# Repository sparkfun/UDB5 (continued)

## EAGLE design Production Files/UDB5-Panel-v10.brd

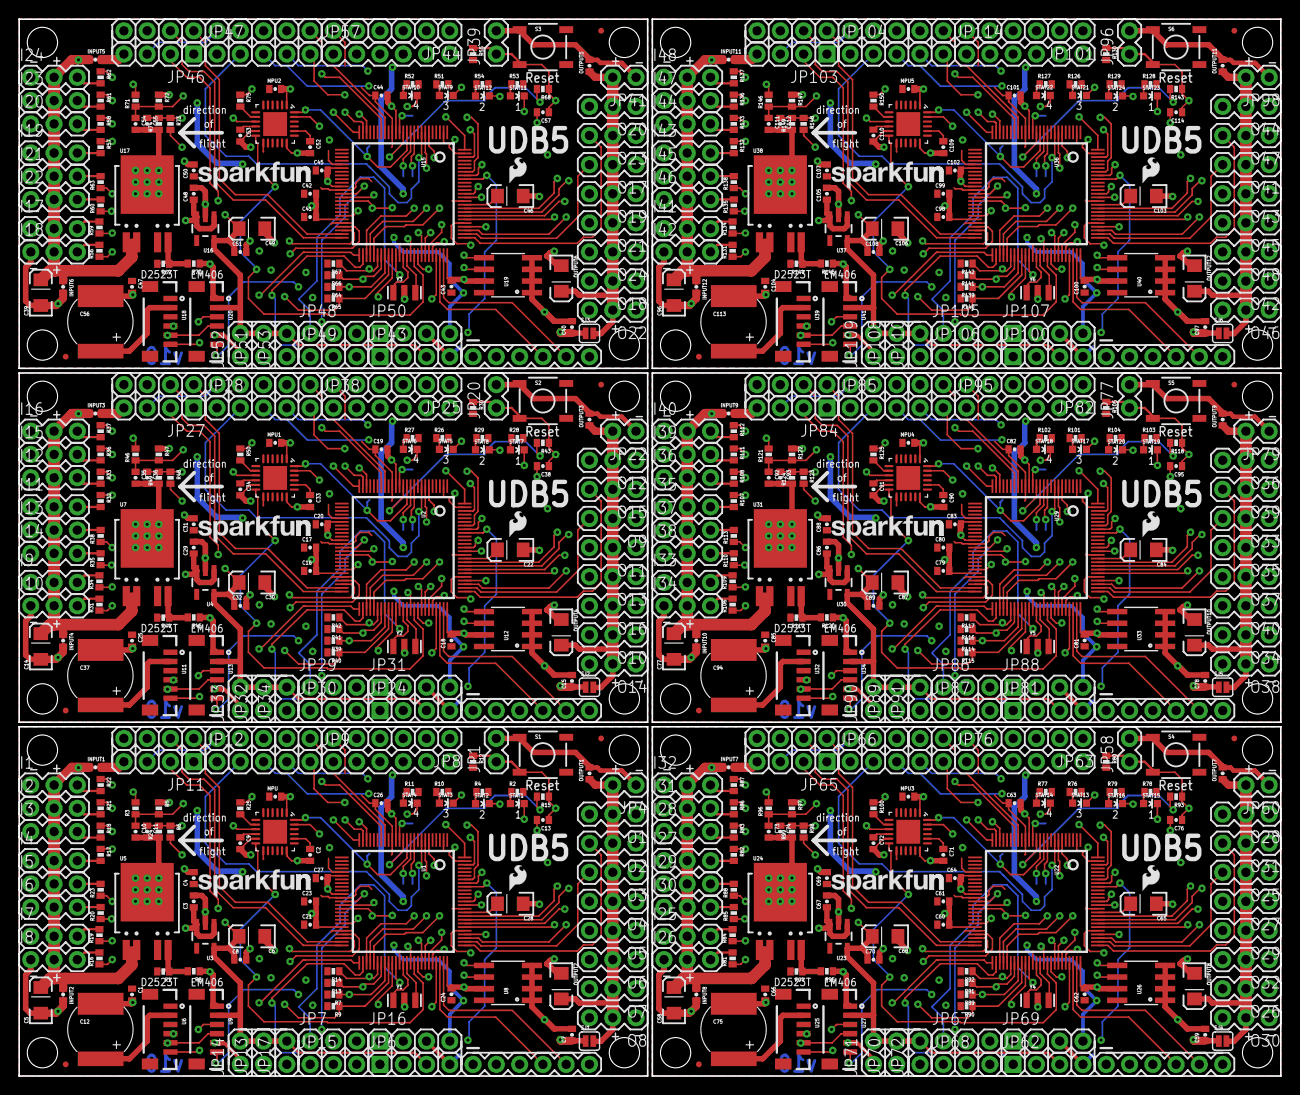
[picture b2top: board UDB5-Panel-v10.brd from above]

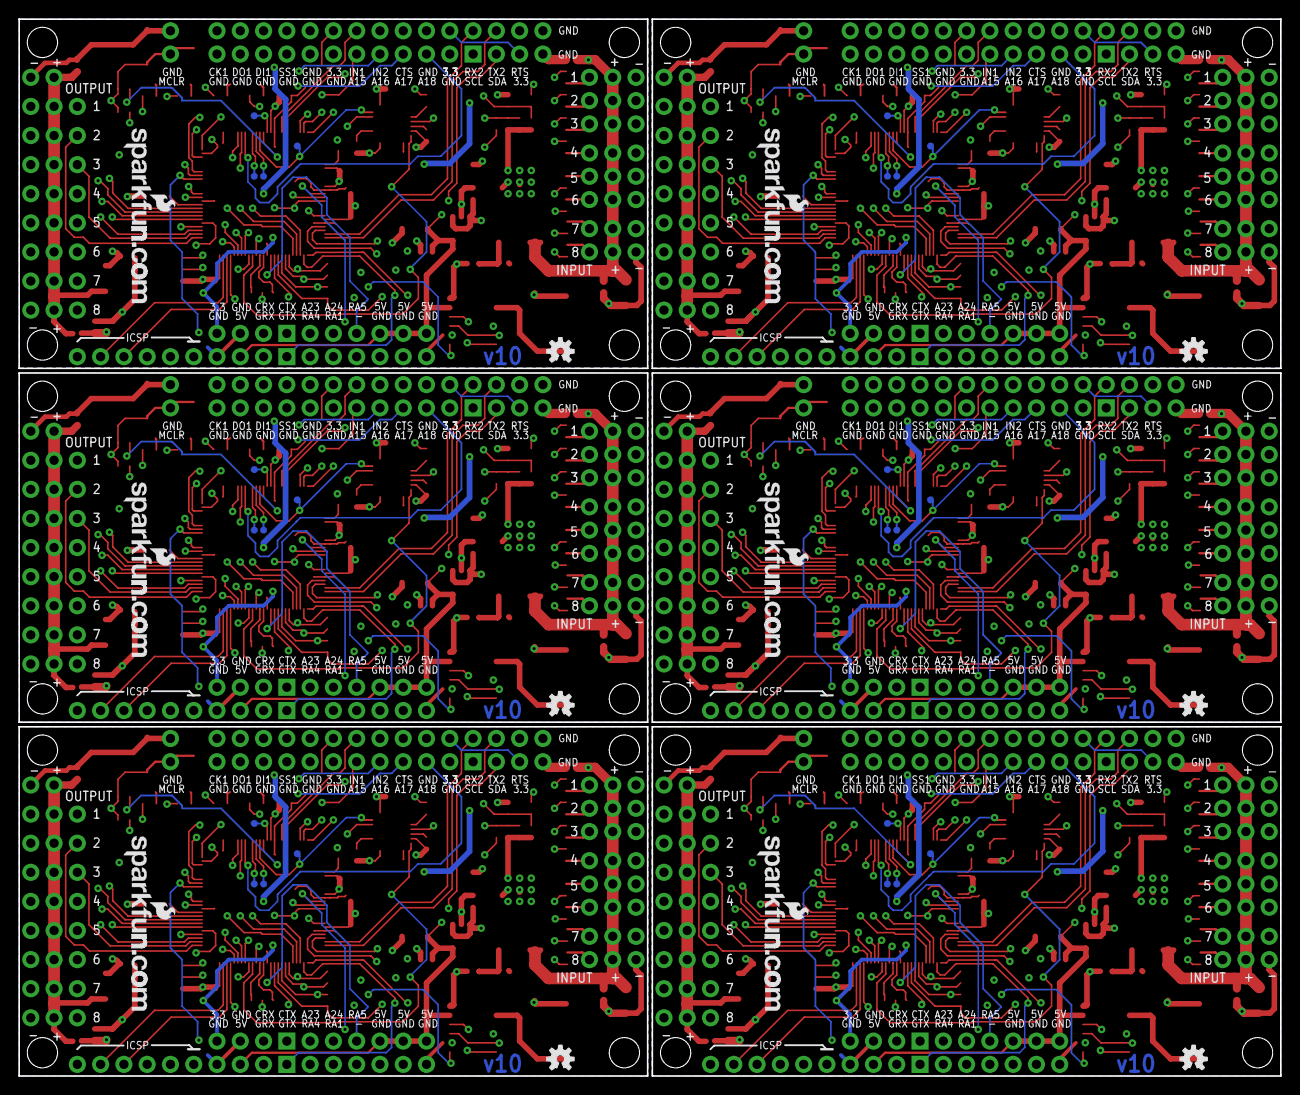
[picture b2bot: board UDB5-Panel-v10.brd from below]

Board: 4 copper layers, 137.7 x 115.3 mm, 654 parts (36 on the bottom side), 504 nets.

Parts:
C1, C3, C25, C29, C47, C48, C66, C67, C85, C86, C104, C105: 1uF; 0402-CAP
C2, C33, C52, C71, C90, C109: 2.2nF; 0402-CAP
C4, C7, C8, C9, C13, C15, C16, C17, C18, C19, C20, C21, C23, C24, C26, C27, C31, C32, C34, C38, C40, C41, C42, C43, C44, C45, C50, C51, C53, C57, C59, C60, C61, C62, C63, C64, C69, C70, C72, C76, C78, C79, C80, C81, C82, C83, C88, C89, C91, C95, C97, C98, C99, C100, C101, C102, C107, C108, C110, C114: 0.1uF; 0402-CAP
C5, C6, C14, C22, C28, C30, C39, C46, C49, C58, C65, C68, C77, C84, C87, C96, C103, C106: 10uF; EIA3216
C10, C11, C35, C36, C54, C55, C73, C74, C92, C93, C111, C112: 22nF; 0402-CAP
C12, C37, C56, C75, C94, C113: 0.2F/3.3V; EN_J2
I1, I2, I3, I4, I5, I6, I7, I8, I9, I10, I11, I12, I13, I14, I15, I16, I17, I18, I19, I20, I21, I22, I23, I24, I25, I26, I27, I28, I29, I30, I31, I32, I33, I34, I35, I36, I37, I38, I39, I40, I41, I42, I43, I44, I45, I46, I47, I48: S; 1X03
INPUT1, INPUT2, INPUT3, INPUT4, INPUT5, INPUT6, INPUT7, INPUT8, INPUT9, INPUT10, INPUT11, INPUT12: 0.1uF; 0402-CAP
JP1, JP20, JP39, JP58, JP77, JP96: EXT_Reset; 1X02
JP2, JP21, JP40, JP59, JP78, JP97: prog; 1X06
JP3, JP35, JP54, JP73, JP92, JP111: LOGO-SFENEW; SFE-NEW-WEBLOGO
JP4, JP22, JP41, JP60, JP79, JP98: SVCC; 1X02
JP5, JP23, JP42, JP61, JP80, JP99: ST; 1X07
JP6, JP24, JP43, JP62, JP81, JP100: SG; 1X04
JP7, JP15, JP29, JP30, JP48, JP49, JP67, JP68, JP86, JP87, JP105, JP106: extra; 1X03
JP8, JP25, JP44, JP63, JP82, JP101: SPI1; 1X06
JP9, JP38, JP57, JP76, JP95, JP114: GND; 1X06
JP10, JP26, JP45, JP64, JP83, JP102: INT; 1X02
JP11, JP27, JP46, JP65, JP84, JP103: I2C; 1X04
JP12, JP28, JP47, JP66, JP85, JP104: ACOM1; 1X05
JP13, JP14, JP17, JP32, JP33, JP34, JP51, JP52, JP53, JP70, JP71, JP72, JP89, JP90, JP91, JP108, JP109, JP110: power; 1X02
JP16, JP31, JP50, JP69, JP88, JP107: extra; 1X04
JP18, JP19, JP36, JP37, JP55, JP56, JP74, JP75, JP93, JP94, JP112, JP113: FIDUCIAL1X2.5; FIDUCIAL-1X2.5
LOGO1, LOGO2, LOGO3, LOGO4, LOGO5, LOGO6: LOGO-SFENW2; SFE-NEW-WEB
MPU, MPU1, MPU2, MPU3, MPU4, MPU5: 0.1uF; 0402-CAP
O1, O2, O3, O4, O5, O6, O7, O8, O9, O10, O11, O12, O13, O14, O15, O16, O17, O18, O19, O20, O21, O22, O23, O24, O25, O26, O27, O28, O29, O30, O31, O32, O33, O34, O35, O36, O37, O38, O39, O40, O41, O42, O43, O44, O45, O46, O47, O48: RA; 1X03
OUTPUT1, OUTPUT3, OUTPUT5, OUTPUT7, OUTPUT9, OUTPUT11: 0.1uF; 0402-CAP
OUTPUT2, OUTPUT4, OUTPUT6, OUTPUT8, OUTPUT10, OUTPUT12: 10uF; EIA3216
R1, R44, R69, R94, R119, R144: 20k; 0402-RES
R2, R4, R10, R11, R16, R17, R18, R19, R20, R21, R22, R23, R26, R27, R28, R29, R31, R32, R33, R34, R35, R36, R37, R38, R51, R52, R53, R54, R56, R57, R58, R59, R60, R61, R62, R63, R76, R77, R78, R79, R81, R82, R83, R84, R85, R86, R87, R88, R101, R102, R103, R104, R106, R107, R108, R109, R110, R111, R112, R113, R126, R127, R128, R129, R131, R132, R133, R134, R135, R136, R137, R138: 330; 0402-RES
R3, R5, R6, R12, R24, R30, R46, R47, R48, R49, R55, R71, R72, R73, R74, R80, R96, R97, R98, R99, R105, R121, R122, R123, R124, R130, R146, R147, R148, R149: 10k; 0402-RES
R7, R9, R13, R14, R39, R40, R41, R42, R64, R65, R66, R67, R89, R90, R91, R92, R114, R115, R116, R117, R139, R140, R141, R142: 4.7k; 0402-RES
R8, R45, R70, R95, R120, R145: 12.1k; 0402-RES
R15, R43, R68, R93, R118, R143: 470; 0402-RES
R25, R50, R75, R100, R125, R150: 1k; 0402-RES
S1, S2, S3, S4, S5, S6: SWITCH-MOMENTARY-2SMD; TACTILE_SWITCH_SMD
SJ1, SJ2, SJ3, SJ4, SJ5, SJ6: SOLDERJUMPERNC; SJ_2S
STAT1, STAT7, STAT11, STAT15, STAT19, STAT23: red; LED-0603
STAT2, STAT8, STAT12, STAT16, STAT20, STAT24: green; LED-0603
STAT3, STAT5, STAT9, STAT13, STAT17, STAT21: yellow; LED-0603
STAT4, STAT6, STAT10, STAT14, STAT18, STAT22: blue; LED-0603
TP1, TP2, TP3, TP4, TP5, TP6, TP7, TP8, TP9, TP10, TP11, TP12, TP13, TP14, TP15, TP16, TP17, TP18, TP19, TP20, TP21, TP22, TP23, TP24: TEST-POINT3; PAD.03X.03
U1, U2, U15, U22, U29, U36: DSPIC33FJ256GP710_; TQFP-100-12X12MM
U3, U4, U16, U23, U30, U37: V_REG_LDOSMD; SOT23-5
U5, U7, U17, U24, U31, U38: V_REG_NCP50X; DPAK-5
U6, U11, U18, U25, U32, U39: D2523T_; EM406
U8, U12, U19, U26, U33, U40: EEPROM-I2CSMD; SO08
U9, U13, U20, U27, U34, U41: EM406
U10, U14, U21, U28, U35, U42: MPU-6000QFN-24; QFN-24-TESTING
U$1, U$2, U$3, U$4, U$5, U$6, U$7, U$8, U$13, U$14, U$15, U$16, U$19, U$20, U$21, U$22, U$25, U$26, U$27, U$28, U$31, U$32, U$33, U$34: STAND-OFF
U$9, U$12, U$18, U$24, U$30, U$36: OSHW-LOGOS; OSHW-LOGO-S
U$10, U$11, U$17, U$23, U$29, U$35: LOGO-SFESK; SFE-LOGO-FLAME
Y1, Y2, Y3, Y4, Y5, Y6: RESONATORSMD; RESONATOR-SMD

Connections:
3.3V: C1.1, C4.1, C21.1, C23.1, C24.1, C26.1, C27.1, JP2.5, JP5.5, JP8.6, JP11.3, JP16.4, MPU.1, R1.2, R2.2, R4.2, R7.2, R9.2, R10.2, R11.2, R12.2, R13.2, R14.2, U1.2, U1.16, U1.30, U1.37, U1.46, U1.62, U1.86, U5.VOUT, U6.3, U8.8, U10.13
3.3V1: C16.1, C17.1, C18.1, C19.1, C20.1, C25.1, C31.1, JP21.5, JP23.5, JP25.6, JP27.3, JP31.4, MPU1.1, R26.2, R27.2, R28.2, R29.2, R30.2, R39.2, R40.2, R41.2, R42.2, R44.2, U2.2, U2.16, U2.30, U2.37, U2.46, U2.62, U2.86, U7.VOUT, U11.3, U12.8, U14.13
3.3V2: C41.1, C42.1, C43.1, C44.1, C45.1, C47.1, C50.1, JP40.5, JP42.5, JP44.6, JP46.3, JP50.4, MPU2.1, R51.2, R52.2, R53.2, R54.2, R55.2, R64.2, R65.2, R66.2, R67.2, R69.2, U15.2, U15.16, U15.30, U15.37, U15.46, U15.62, U15.86, U17.VOUT, U18.3, U19.8, U21.13
3.3V3: C60.1, C61.1, C62.1, C63.1, C64.1, C66.1, C69.1, JP59.5, JP61.5, JP63.6, JP65.3, JP69.4, MPU3.1, R76.2, R77.2, R78.2, R79.2, R80.2, R89.2, R90.2, R91.2, R92.2, R94.2, U22.2, U22.16, U22.30, U22.37, U22.46, U22.62, U22.86, U24.VOUT, U25.3, U26.8, U28.13
3.3V4: C79.1, C80.1, C81.1, C82.1, C83.1, C85.1, C88.1, JP78.5, JP80.5, JP82.6, JP84.3, JP88.4, MPU4.1, R101.2, R102.2, R103.2, R104.2, R105.2, R114.2, R115.2, R116.2, R117.2, R119.2, U29.2, U29.16, U29.30, U29.37, U29.46, U29.62, U29.86, U31.VOUT, U32.3, U33.8, U35.13
3.3V5: C98.1, C99.1, C100.1, C101.1, C102.1, C104.1, C107.1, JP97.5, JP99.5, JP101.6, JP103.3, JP107.4, MPU5.1, R126.2, R127.2, R128.2, R129.2, R130.2, R139.2, R140.2, R141.2, R142.2, R144.2, U36.2, U36.16, U36.30, U36.37, U36.46, U36.62, U36.86, U38.VOUT, U39.3, U40.8, U42.13
5V: C6.A, C8.1, JP6.3, JP13.2, JP14.2, JP17.2, R6.2, U3.5, U9.2
5V1: C30.A, C32.1, JP24.3, JP32.2, JP33.2, JP34.2, R48.2, U4.5, U13.2
5V2: C49.A, C51.1, JP43.3, JP51.2, JP52.2, JP53.2, R73.2, U16.5, U20.2
5V3: C68.A, C70.1, JP62.3, JP70.2, JP71.2, JP72.2, R98.2, U23.5, U27.2
5V4: C87.A, C89.1, JP81.3, JP89.2, JP90.2, JP91.2, R123.2, U30.5, U34.2
5V5: C106.A, C108.1, JP100.3, JP108.2, JP109.2, JP110.2, R148.2, U37.5, U41.2
A-5V: C11.1, R6.1, R24.2, U1.24
A-5V1: C36.1, R48.1, R49.2, U2.24
A-5V2: C55.1, R73.1, R74.2, U15.24
A-5V3: C74.1, R98.1, R99.2, U22.24
A-5V4: C93.1, R123.1, R124.2, U29.24
A-5V5: C112.1, R148.1, R149.2, U36.24
A-VCC: C10.1, R3.1, R5.2, U1.25
A-VCC1: C35.1, R46.1, R47.2, U2.25
A-VCC2: C54.1, R71.1, R72.2, U15.25
A-VCC3: C73.1, R96.1, R97.2, U22.25
A-VCC4: C92.1, R121.1, R122.2, U29.25
A-VCC5: C111.1, R146.1, R147.2, U36.25
AN1: JP28.5, U2.44
AN2: JP28.4, U2.6
AN3: JP28.3, U2.7
AN4: JP29.2, U2.93
AN5: JP28.2, U2.8
AN6: JP29.3, U2.92
AN7: JP47.5, U15.44
AN8: JP47.4, U15.6
AN9: JP47.3, U15.7
AN10: JP48.2, U15.93
AN11: JP47.2, U15.8
AN12: JP48.3, U15.92
AN13: JP66.5, U22.44
AN14: JP66.4, U22.6
AN15: JP12.5, U1.44
AN16: JP12.4, U1.6
AN17: JP12.3, U1.7
AN18: JP12.2, U1.8
AN19: JP66.3, U22.7
AN20: JP67.2, U22.93
AN21: JP66.2, U22.8
AN22: JP67.3, U22.92
AN23: JP7.3, U1.92
AN24: JP7.2, U1.93
AN25: JP85.5, U29.44
AN26: JP85.4, U29.6
AN27: JP85.3, U29.7
AN28: JP86.2, U29.93
AN29: JP85.2, U29.8
AN30: JP86.3, U29.92
AN31: JP104.5, U36.44
AN32: JP104.4, U36.6
AN33: JP104.3, U36.7
AN34: JP105.2, U36.93
AN35: JP104.2, U36.8
AN36: JP105.3, U36.92
CRX: JP16.2, U1.87
CRX1: JP31.2, U2.87
CRX2: JP50.2, U15.87
CRX3: JP69.2, U22.87
CRX4: JP88.2, U29.87
CRX5: JP107.2, U36.87
CTS1: JP23.7, U2.40
CTS2: JP5.7, U1.40
CTS3: JP42.7, U15.40
CTS4: JP61.7, U22.40
CTS5: JP80.7, U29.40
CTS6: JP99.7, U36.40
CTX: JP16.1, U1.88
CTX1: JP31.1, U2.88
CTX2: JP50.1, U15.88
CTX3: JP69.1, U22.88
CTX4: JP88.1, U29.88
CTX5: JP107.1, U36.88
GND: C1.2, C2.2, C3.2, C4.2, C5.C, C6.C, C7.2, C8.2, C9.2, C10.2, C11.2, C12.-, C13.2, C21.2, C23.2, C24.2, C26.2, C27.2, C28.C, I1.1, I2.1, I3.1, I4.1, I5.1, I6.1, I7.1, I8.1, INPUT1.2, INPUT2.2, JP1.2, JP2.4, JP4.1, JP5.1, JP5.6, JP6.4, JP8.5, JP9.1, JP9.2, JP9.3, JP9.4, JP9.5, JP9.6, JP11.4, JP12.1, JP13.1, JP14.1, JP16.3, JP17.1, MPU.2, O1.1, O2.1, O3.1, O4.1, O5.1, O6.1, O7.1, O8.1, OUTPUT1.2, OUTPUT2.C, R5.1, R8.1, R24.1, S1.1, U1.15, U1.31, U1.36, U1.45, U1.65, U1.75, U3.2, U5.GND, U6.4, U8.1, U8.2, U8.3, U8.4, U8.7, U9.1, U9.5, U10.1, U10.11, U10.18, Y1.2
GND1: C14.C, C15.2, C16.2, C17.2, C18.2, C19.2, C20.2, C22.C, C25.2, C29.2, C30.C, C31.2, C32.2, C33.2, C34.2, C35.2, C36.2, C37.-, C38.2, I9.1, I10.1, I11.1, I12.1, I13.1, I14.1, I15.1, I16.1, INPUT3.2, INPUT4.2, JP20.2, JP21.4, JP22.1, JP23.1, JP23.6, JP24.4, JP25.5, JP27.4, JP28.1, JP31.3, JP32.1, JP33.1, JP34.1, JP38.1, JP38.2, JP38.3, JP38.4, JP38.5, JP38.6, MPU1.2, O9.1, O10.1, O11.1, O12.1, O13.1, O14.1, O15.1, O16.1, OUTPUT3.2, OUTPUT4.C, R45.1, R47.1, R49.1, S2.1, U2.15, U2.31, U2.36, U2.45, U2.65, U2.75, U4.2, U7.GND, U11.4, U12.1, U12.2, U12.3, U12.4, U12.7, U13.1, U13.5, U14.1, U14.11, U14.18, Y2.2
GND2: C39.C, C40.2, C41.2, C42.2, C43.2, C44.2, C45.2, C46.C, C47.2, C48.2, C49.C, C50.2, C51.2, C52.2, C53.2, C54.2, C55.2, C56.-, C57.2, I17.1, I18.1, I19.1, I20.1, I21.1, I22.1, I23.1, I24.1, INPUT5.2, INPUT6.2, JP39.2, JP40.4, JP41.1, JP42.1, JP42.6, JP43.4, JP44.5, JP46.4, JP47.1, JP50.3, JP51.1, JP52.1, JP53.1, JP57.1, JP57.2, JP57.3, JP57.4, JP57.5, JP57.6, MPU2.2, O17.1, O18.1, O19.1, O20.1, O21.1, O22.1, O23.1, O24.1, OUTPUT5.2, OUTPUT6.C, R70.1, R72.1, R74.1, S3.1, U15.15, U15.31, U15.36, U15.45, U15.65, U15.75, U16.2, U17.GND, U18.4, U19.1, U19.2, U19.3, U19.4, U19.7, U20.1, U20.5, U21.1, U21.11, U21.18, Y3.2
GND3: C58.C, C59.2, C60.2, C61.2, C62.2, C63.2, C64.2, C65.C, C66.2, C67.2, C68.C, C69.2, C70.2, C71.2, C72.2, C73.2, C74.2, C75.-, C76.2, I25.1, I26.1, I27.1, I28.1, I29.1, I30.1, I31.1, I32.1, INPUT7.2, INPUT8.2, JP58.2, JP59.4, JP60.1, JP61.1, JP61.6, JP62.4, JP63.5, JP65.4, JP66.1, JP69.3, JP70.1, JP71.1, JP72.1, JP76.1, JP76.2, JP76.3, JP76.4, JP76.5, JP76.6, MPU3.2, O25.1, O26.1, O27.1, O28.1, O29.1, O30.1, O31.1, O32.1, OUTPUT7.2, OUTPUT8.C, R95.1, R97.1, R99.1, S4.1, U22.15, U22.31, U22.36, U22.45, U22.65, U22.75, U23.2, U24.GND, U25.4, U26.1, U26.2, U26.3, U26.4, U26.7, U27.1, U27.5, U28.1, U28.11, U28.18, Y4.2
GND4: C77.C, C78.2, C79.2, C80.2, C81.2, C82.2, C83.2, C84.C, C85.2, C86.2, C87.C, C88.2, C89.2, C90.2, C91.2, C92.2, C93.2, C94.-, C95.2, I33.1, I34.1, I35.1, I36.1, I37.1, I38.1, I39.1, I40.1, INPUT9.2, INPUT10.2, JP77.2, JP78.4, JP79.1, JP80.1, JP80.6, JP81.4, JP82.5, JP84.4, JP85.1, JP88.3, JP89.1, JP90.1, JP91.1, JP95.1, JP95.2, JP95.3, JP95.4, JP95.5, JP95.6, MPU4.2, O33.1, O34.1, O35.1, O36.1, O37.1, O38.1, O39.1, O40.1, OUTPUT9.2, OUTPUT10.C, R120.1, R122.1, R124.1, S5.1, U29.15, U29.31, U29.36, U29.45, U29.65, U29.75, U30.2, U31.GND, U32.4, U33.1, U33.2, U33.3, U33.4, U33.7, U34.1, U34.5, U35.1, U35.11, U35.18, Y5.2
GND5: C96.C, C97.2, C98.2, C99.2, C100.2, C101.2, C102.2, C103.C, C104.2, C105.2, C106.C, C107.2, C108.2, C109.2, C110.2, C111.2, C112.2, C113.-, C114.2, I41.1, I42.1, I43.1, I44.1, I45.1, I46.1, I47.1, I48.1, INPUT11.2, INPUT12.2, JP96.2, JP97.4, JP98.1, JP99.1, JP99.6, JP100.4, JP101.5, JP103.4, JP104.1, JP107.3, JP108.1, JP109.1, JP110.1, JP114.1, JP114.2, JP114.3, JP114.4, JP114.5, JP114.6, MPU5.2, O41.1, O42.1, O43.1, O44.1, O45.1, O46.1, O47.1, O48.1, OUTPUT11.2, OUTPUT12.C, R145.1, R147.1, R149.1, S6.1, U36.15, U36.31, U36.36, U36.45, U36.65, U36.75, U37.2, U38.GND, U39.4, U40.1, U40.2, U40.3, U40.4, U40.7, U41.1, U41.5, U42.1, U42.11, U42.18, Y6.2
GPS_PPS: U1.67, U9.6
GPS_PPS1: U2.67, U13.6
GPS_PPS2: U15.67, U20.6
GPS_PPS3: U22.67, U27.6
GPS_PPS4: U29.67, U34.6
GPS_PPS5: U36.67, U41.6
GPS_RX: JP6.2, U1.51, U6.6, U9.3
GPS_RX1: JP24.2, U2.51, U11.6, U13.3
GPS_RX2: JP43.2, U15.51, U18.6, U20.3
GPS_RX3: JP62.2, U22.51, U25.6, U27.3
GPS_RX4: JP81.2, U29.51, U32.6, U34.3
GPS_RX5: JP100.2, U36.51, U39.6, U41.3
GPS_TX: JP6.1, U1.52, U6.5, U9.4
GPS_TX1: JP24.1, U2.52, U11.5, U13.4
GPS_TX2: JP43.1, U15.52, U18.5, U20.4
GPS_TX3: JP62.1, U22.52, U25.5, U27.4
GPS_TX4: JP81.1, U29.52, U32.5, U34.4
GPS_TX5: JP100.1, U36.52, U39.5, U41.4
I1: R22.1, U1.68
I2: R21.1, U1.69
I3: R18.1, U1.70
I4: R17.1, U1.71
I5: R23.1, U1.79
I6: R20.1, U1.80
I7: R19.1, U1.47
I8: R16.1, U1.48
I9: R37.1, U2.68
I10: R36.1, U2.69
I11: R33.1, U2.70
I12: R32.1, U2.71
I13: R38.1, U2.79
I14: R35.1, U2.80
I15: R34.1, U2.47
I16: R31.1, U2.48
I17: R62.1, U15.68
I18: R61.1, U15.69
I19: R58.1, U15.70
I20: R57.1, U15.71
I21: R63.1, U15.79
I22: R60.1, U15.80
I23: R59.1, U15.47
I24: R56.1, U15.48
I25: R87.1, U22.68
I26: R86.1, U22.69
I27: R83.1, U22.70
I28: R82.1, U22.71
I29: R88.1, U22.79
I30: R85.1, U22.80
I31: R84.1, U22.47
I32: R81.1, U22.48
I33: R112.1, U29.68
I34: R111.1, U29.69
I35: R108.1, U29.70
I36: R107.1, U29.71
I37: R113.1, U29.79
I38: R110.1, U29.80
I39: R109.1, U29.47
I40: R106.1, U29.48
I41: R137.1, U36.68
I42: R136.1, U36.69
I43: R133.1, U36.70
I44: R132.1, U36.71
I45: R138.1, U36.79
I46: R135.1, U36.80
I47: R134.1, U36.47
I48: R131.1, U36.48
INT1: JP10.2, U1.18
INT2: JP10.1, U1.19
INT3: JP26.2, U2.18
INT4: JP26.1, U2.19
INT5: JP45.2, U15.18
INT6: JP45.1, U15.19
INT7: JP64.2, U22.18
INT8: JP64.1, U22.19
INT9: JP83.2, U29.18
INT10: JP83.1, U29.19
INT11: JP102.2, U36.18
INT12: JP102.1, U36.19
LED1: STAT1.C, U1.94
LED2: STAT2.C, U1.98
LED3: STAT3.C, U1.99
LED4: STAT4.C, U1.100
LED5: STAT7.C, U2.94
LED6: STAT8.C, U2.98
LED7: STAT5.C, U2.99
LED8: STAT6.C, U2.100
LED9: STAT11.C, U15.94
LED10: STAT12.C, U15.98
LED11: STAT9.C, U15.99
LED12: STAT10.C, U15.100
LED13: STAT15.C, U22.94
LED14: STAT16.C, U22.98
LED15: STAT13.C, U22.99
LED16: STAT14.C, U22.100
LED17: STAT19.C, U29.94
LED18: STAT20.C, U29.98
LED19: STAT17.C, U29.99
LED20: STAT18.C, U29.100
LED21: STAT23.C, U36.94
LED22: STAT24.C, U36.98
LED23: STAT21.C, U36.99
LED24: STAT22.C, U36.100
MCLR: C13.1, JP1.1, JP2.6, R12.1, R15.1, S1.3
MCLR1: C38.1, JP20.1, JP21.6, R30.1, R43.1, S2.3
MCLR2: C57.1, JP39.1, JP40.6, R55.1, R68.1, S3.3
MCLR3: C76.1, JP58.1, JP59.6, R80.1, R93.1, S4.3
MCLR4: C95.1, JP77.1, JP78.6, R105.1, R118.1, S5.3
MCLR5: C114.1, JP96.1, JP97.6, R130.1, R143.1, S6.3
MPU-CS: R25.1, TP1.P$1, U1.14
MPU-CS1: R50.1, TP5.P$1, U2.14
MPU-CS2: R75.1, TP9.P$1, U15.14
MPU-CS3: R100.1, TP13.P$1, U22.14
MPU-CS4: R125.1, TP17.P$1, U29.14
MPU-CS5: R150.1, TP21.P$1, U36.14
MPU-INT: U1.66, U10.12
MPU-INT1: U2.66, U14.12
MPU-INT2: U15.66, U21.12
MPU-INT3: U22.66, U28.12
MPU-INT4: U29.66, U35.12
MPU-INT5: U36.66, U42.12
MPU-MISO: TP3.P$1, U1.11, U10.9
MPU-MISO1: TP7.P$1, U2.11, U14.9
MPU-MISO2: TP11.P$1, U15.11, U21.9
MPU-MISO3: TP15.P$1, U22.11, U28.9
MPU-MISO4: TP19.P$1, U29.11, U35.9
MPU-MISO5: TP23.P$1, U36.11, U42.9
MPU-MOSI: TP4.P$1, U1.12, U10.24
MPU-MOSI1: TP8.P$1, U2.12, U14.24
MPU-MOSI2: TP12.P$1, U15.12, U21.24
MPU-MOSI3: TP16.P$1, U22.12, U28.24
MPU-MOSI4: TP20.P$1, U29.12, U35.24
MPU-MOSI5: TP24.P$1, U36.12, U42.24
MPU-SCK: TP2.P$1, U1.10, U10.23
MPU-SCK1: TP6.P$1, U2.10, U14.23
MPU-SCK2: TP10.P$1, U15.10, U21.23
MPU-SCK3: TP14.P$1, U22.10, U28.23
MPU-SCK4: TP18.P$1, U29.10, U35.23
MPU-SCK5: TP22.P$1, U36.10, U42.23
unnamed: R2.1, STAT1.A
unnamed: R4.1, STAT2.A
unnamed: U1.64, Y1.3
unnamed: C12.+, U6.2
unnamed: R25.2, U10.8
unnamed: U1.63, Y1.1
unnamed: R15.2, U1.13
unnamed: R26.1, STAT5.A
unnamed: R1.1, R8.2, U5.ADJ
unnamed: R27.1, STAT6.A
unnamed: R28.1, STAT7.A
unnamed: R29.1, STAT8.A
unnamed: C2.1, U10.20
unnamed: I8.3, R16.2
unnamed: I4.3, R17.2
unnamed: C9.1, U10.10
unnamed: I3.3, R18.2
unnamed: I7.3, R19.2
unnamed: I6.3, R20.2
unnamed: I2.3, R21.2
unnamed: I1.3, R22.2
unnamed: I10.3, R31.2
unnamed: I11.3, R32.2
unnamed: I12.3, R33.2
unnamed: I9.3, R34.2
unnamed: I14.3, R35.2
unnamed: I5.3, R23.2
unnamed: I15.3, R36.2
unnamed: I16.3, R37.2
unnamed: I13.3, R38.2
unnamed: C22.A, U2.85
unnamed: U2.64, Y2.3
unnamed: R10.1, STAT3.A
unnamed: R11.1, STAT4.A
unnamed: C28.A, U1.85
unnamed: U2.63, Y2.1
unnamed: R43.2, U2.13
unnamed: R44.1, R45.2, U7.ADJ
unnamed: C33.1, U14.20
unnamed: C34.1, U14.10
unnamed: C37.+, U11.2
unnamed: R50.2, U14.8
unnamed: R51.1, STAT9.A
unnamed: R52.1, STAT10.A
unnamed: R53.1, STAT11.A
unnamed: R54.1, STAT12.A
unnamed: I18.3, R56.2
unnamed: I19.3, R57.2
unnamed: I20.3, R58.2
unnamed: I17.3, R59.2
unnamed: I22.3, R60.2
unnamed: I23.3, R61.2
unnamed: I24.3, R62.2
unnamed: I21.3, R63.2
unnamed: C46.A, U15.85
unnamed: U15.64, Y3.3
unnamed: U15.63, Y3.1
unnamed: R68.2, U15.13
unnamed: R69.1, R70.2, U17.ADJ
unnamed: C52.1, U21.20
unnamed: C53.1, U21.10
unnamed: C56.+, U18.2
unnamed: R75.2, U21.8
unnamed: R76.1, STAT13.A
unnamed: R77.1, STAT14.A
unnamed: R78.1, STAT15.A
unnamed: R79.1, STAT16.A
unnamed: I26.3, R81.2
unnamed: I27.3, R82.2
unnamed: I28.3, R83.2
unnamed: I25.3, R84.2
unnamed: I30.3, R85.2
unnamed: I31.3, R86.2
unnamed: I32.3, R87.2
unnamed: I29.3, R88.2
unnamed: C65.A, U22.85
unnamed: U22.64, Y4.3
unnamed: U22.63, Y4.1
unnamed: R93.2, U22.13
unnamed: R94.1, R95.2, U24.ADJ
unnamed: C71.1, U28.20
unnamed: C72.1, U28.10
unnamed: C75.+, U25.2
unnamed: R100.2, U28.8
unnamed: R101.1, STAT17.A
unnamed: R102.1, STAT18.A
unnamed: R103.1, STAT19.A
unnamed: R104.1, STAT20.A
unnamed: I34.3, R106.2
unnamed: I35.3, R107.2
unnamed: I36.3, R108.2
unnamed: I33.3, R109.2
unnamed: I38.3, R110.2
unnamed: I39.3, R111.2
unnamed: I40.3, R112.2
unnamed: I37.3, R113.2
unnamed: C84.A, U29.85
unnamed: U29.64, Y5.3
unnamed: U29.63, Y5.1
unnamed: R118.2, U29.13
unnamed: R119.1, R120.2, U31.ADJ
unnamed: C90.1, U35.20
unnamed: C91.1, U35.10
unnamed: C94.+, U32.2
unnamed: R125.2, U35.8
unnamed: R126.1, STAT21.A
unnamed: R127.1, STAT22.A
unnamed: R128.1, STAT23.A
unnamed: R129.1, STAT24.A
unnamed: I42.3, R131.2
unnamed: I43.3, R132.2
unnamed: I44.3, R133.2
unnamed: I41.3, R134.2
unnamed: I46.3, R135.2
unnamed: I47.3, R136.2
unnamed: I48.3, R137.2
unnamed: I45.3, R138.2
unnamed: C103.A, U36.85
unnamed: U36.64, Y6.3
unnamed: U36.63, Y6.1
unnamed: R143.2, U36.13
unnamed: R144.1, R145.2, U38.ADJ
unnamed: C109.1, U42.20
unnamed: C110.1, U42.10
unnamed: C113.+, U39.2
unnamed: R150.2, U42.8
O1: O1.3, U1.72
O2: O2.3, U1.76
O3: O3.3, U1.77
O4: O4.3, U1.78
O5: O5.3, U1.81
O6: O6.3, U1.82
O7: O7.3, U1.83
O8: O8.3, U1.84
O9: O12.3, U2.72
O10: O15.3, U2.76
O11: O9.3, U2.77
O12: O11.3, U2.78
O13: O13.3, U2.81
O14: O16.3, U2.82
O15: O10.3, U2.83
O16: O14.3, U2.84
O17: O20.3, U15.72
O18: O23.3, U15.76
O19: O17.3, U15.77
O20: O19.3, U15.78
O21: O21.3, U15.81
O22: O24.3, U15.82
O23: O18.3, U15.83
O24: O22.3, U15.84
O25: O28.3, U22.72
O26: O31.3, U22.76
O27: O25.3, U22.77
O28: O27.3, U22.78
O29: O29.3, U22.81
O30: O32.3, U22.82
O31: O26.3, U22.83
O32: O30.3, U22.84
O33: O36.3, U29.72
O34: O39.3, U29.76
O35: O33.3, U29.77
O36: O35.3, U29.78
O37: O37.3, U29.81
O38: O40.3, U29.82
O39: O34.3, U29.83
O40: O38.3, U29.84
O41: O44.3, U36.72
O42: O47.3, U36.76
O43: O41.3, U36.77
O44: O43.3, U36.78
O45: O45.3, U36.81
O46: O48.3, U36.82
O47: O42.3, U36.83
O48: O46.3, U36.84
PGEC1: JP21.2, U2.74
PGEC2: JP2.2, U1.74
PGEC3: JP40.2, U15.74
PGEC4: JP59.2, U22.74
PGEC5: JP78.2, U29.74
PGEC6: JP97.2, U36.74
PGED1: JP21.3, U2.73
PGED2: JP2.3, U1.73
PGED3: JP40.3, U15.73
PGED4: JP59.3, U22.73
PGED5: JP78.3, U29.73
PGED6: JP97.3, U36.73
RA1: JP15.2, U1.38
RA2: JP29.1, U2.61
RA3: JP30.3, U2.60
RA4: JP15.3, U1.60
RA5: JP7.1, U1.61
RA6: JP30.2, U2.38
RA7: JP48.1, U15.61
RA8: JP49.3, U15.60
RA9: JP49.2, U15.38
RA10: JP67.1, U22.61
RA11: JP68.3, U22.60
RA12: JP68.2, U22.38
RA13: JP86.1, U29.61
RA14: JP87.3, U29.60
RA15: JP87.2, U29.38
RA16: JP105.1, U36.61
RA17: JP106.3, U36.60
RA18: JP106.2, U36.38
RTS1: JP23.2, U2.39
RTS2: JP5.2, U1.39
RTS3: JP42.2, U15.39
RTS4: JP61.2, U22.39
RTS5: JP80.2, U29.39
RTS6: JP99.2, U36.39
RX1: JP23.4, U2.49
RX2: JP5.4, U1.49
RX3: JP42.4, U15.49
RX4: JP61.4, U22.49
RX5: JP80.4, U29.49
RX6: JP99.4, U36.49
SCK1: JP8.1, U1.55
SCK2: JP25.1, U2.55
SCK3: JP44.1, U15.55
SCK4: JP63.1, U22.55
SCK5: JP82.1, U29.55
SCK6: JP101.1, U36.55
SCL1: R13.1, U1.57, U8.6
SCL2: JP11.1, R7.1, U1.58
SCL3: R41.1, U2.57, U12.6
SCL4: JP27.1, R39.1, U2.58
SCL5: R66.1, U15.57, U19.6
SCL6: JP46.1, R64.1, U15.58
SCL7: R91.1, U22.57, U26.6
SCL8: JP65.1, R89.1, U22.58
SCL9: R116.1, U29.57, U33.6
SCL10: JP84.1, R114.1, U29.58
SCL11: R141.1, U36.57, U40.6
SCL12: JP103.1, R139.1, U36.58
SDA1: R14.1, U1.56, U8.5
SDA2: JP11.2, R9.1, U1.59
SDA3: R42.1, U2.56, U12.5
SDA4: JP27.2, R40.1, U2.59
SDA5: R67.1, U15.56, U19.5
SDA6: JP46.2, R65.1, U15.59
SDA7: R92.1, U22.56, U26.5
SDA8: JP65.2, R90.1, U22.59
SDA9: R117.1, U29.56, U33.5
SDA10: JP84.2, R115.1, U29.59
SDA11: R142.1, U36.56, U40.5
SDA12: JP103.2, R140.1, U36.59
SDI1: JP8.3, U1.54
SDI2: JP25.3, U2.54
SDI3: JP44.3, U15.54
SDI4: JP63.3, U22.54
SDI5: JP82.3, U29.54
SDI6: JP101.3, U36.54
SDO1: JP8.2, U1.53
SDO2: JP25.2, U2.53
SDO3: JP44.2, U15.53
SDO4: JP63.2, U22.53
SDO5: JP82.2, U29.53
SDO6: JP101.2, U36.53
SS1: JP8.4, U1.23
SS2: JP25.4, U2.23
SS3: JP44.4, U15.23
SS4: JP63.4, U22.23
SS5: JP82.4, U29.23
SS6: JP101.4, U36.23
SVCC: JP4.2, O1.2, O2.2, O3.2, O4.2, O5.2, O6.2, O7.2, O8.2, OUTPUT1.1, OUTPUT2.A, SJ1.2
SVCC1: JP22.2, O9.2, O10.2, O11.2, O12.2, O13.2, O14.2, O15.2, O16.2, OUTPUT3.1, OUTPUT4.A, SJ2.2
SVCC2: JP41.2, O17.2, O18.2, O19.2, O20.2, O21.2, O22.2, O23.2, O24.2, OUTPUT5.1, OUTPUT6.A, SJ3.2
SVCC3: JP60.2, O25.2, O26.2, O27.2, O28.2, O29.2, O30.2, O31.2, O32.2, OUTPUT7.1, OUTPUT8.A, SJ4.2
SVCC4: JP79.2, O33.2, O34.2, O35.2, O36.2, O37.2, O38.2, O39.2, O40.2, OUTPUT9.1, OUTPUT10.A, SJ5.2
SVCC5: JP98.2, O41.2, O42.2, O43.2, O44.2, O45.2, O46.2, O47.2, O48.2, OUTPUT11.1, OUTPUT12.A, SJ6.2
TX1: JP23.3, U2.50
TX2: JP5.3, U1.50
TX3: JP42.3, U15.50
TX4: JP61.3, U22.50
TX5: JP80.3, U29.50
TX6: JP99.3, U36.50
VCC: C3.1, C5.A, C7.1, I1.2, I2.2, I3.2, I4.2, I5.2, I6.2, I7.2, I8.2, INPUT1.1, INPUT2.1, R3.2, SJ1.1, U3.1, U3.3, U5.EN, U5.VIN
VCC1: C14.A, C15.1, C29.1, I9.2, I10.2, I11.2, I12.2, I13.2, I14.2, I15.2, I16.2, INPUT3.1, INPUT4.1, R46.2, SJ2.1, U4.1, U4.3, U7.EN, U7.VIN
VCC2: C39.A, C40.1, C48.1, I17.2, I18.2, I19.2, I20.2, I21.2, I22.2, I23.2, I24.2, INPUT5.1, INPUT6.1, R71.2, SJ3.1, U16.1, U16.3, U17.EN, U17.VIN
VCC3: C58.A, C59.1, C67.1, I25.2, I26.2, I27.2, I28.2, I29.2, I30.2, I31.2, I32.2, INPUT7.1, INPUT8.1, R96.2, SJ4.1, U23.1, U23.3, U24.EN, U24.VIN
VCC4: C77.A, C78.1, C86.1, I33.2, I34.2, I35.2, I36.2, I37.2, I38.2, I39.2, I40.2, INPUT9.1, INPUT10.1, R121.2, SJ5.1, U30.1, U30.3, U31.EN, U31.VIN
VCC5: C96.A, C97.1, C105.1, I41.2, I42.2, I43.2, I44.2, I45.2, I46.2, I47.2, I48.2, INPUT11.1, INPUT12.1, R146.2, SJ6.1, U37.1, U37.3, U38.EN, U38.VIN

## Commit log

2013-01-25 adding files
2013-01-25 added dru file
2013-01-28 prototype v010
    added gerbers
2013-01-28 edited gitignore
    added .dri, ,gpi, .GML
2013-01-28 added bom
2013-01-28 Deleted gerbers
2013-03-12 v011
    -swapped MPU MOSI and MISO, labeled them correctly.
    -increased silk txt on PCB
2013-04-26 v10
    red board order
2013-04-26 v10
    red board order
    -added readmes
2013-05-02 v10 red boards
    production red boards
2013-05-02 Production files
    created panel for production
2013-07-22 updated readme with photo
